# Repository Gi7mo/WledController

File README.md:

# WLED Controller for 5V LED Strips

*e.g. ws2812b, and only tested with them*

The Power supply is a 100-240VAC one and  rated at 5v 4A, don't exceed the power of the supply. Use e.g. the [WLED power calculator](https://wled-calculator.github.io/)

**As i live in germany, the pcb is only tested with 230V AC, if you supply any other voltage, be warned!**

*It can go up in flames, explode or kill you. It's main power!*

- 

**BOM**
|Reference               |Quantity|Value                                                                                                              |LCSC    |ALI                                              |
|------------------------|--------|-------------------------------------------------------------------------------------------------------------------|--------|-------------------------------------------------|
|C1 C2                   |2       |C                                                                                                                  |C107172 |[Link](https://s.click.aliexpress.com/e/_DkweKyn)|
|J1                      |1       |Conn_01x02_Male                                                                                                    |C475092 |[Link](https://s.click.aliexpress.com/e/_DC1TC2L)|
|J2                      |1       |Conn_01x03_Male                                                                                                    |C475093 |[Link](https://s.click.aliexpress.com/e/_DC1TC2L)|
|J3                      |1       |Conn_01x04_Male                                                                                                    |C2691448|[Link](https://s.click.aliexpress.com/e/_DDO0FkL)|
|Q1                      |1       |BSS138                                                                                                             |C52895  |[Link](https://s.click.aliexpress.com/e/_DF4Oc0f)|
|R1 R2 R3 R4 R5 R6 R7    |7       |10K                                                                                                                |C144471 |[Link](https://s.click.aliexpress.com/e/_Ddns0gR)|
|SW1                     |1       |SW_FLASH                                                                                                           |C393938 |[Link](https://s.click.aliexpress.com/e/_DdksuhH)|
|SW2                     |1       |SW_RESET                                                                                                           |C393938 |[Link](https://s.click.aliexpress.com/e/_DdksuhH)|
|U2                      |1       |AMS1117-3.3                                                                                                        |C5199435|[Link](https://s.click.aliexpress.com/e/_DF2uDUr)|
|U3                      |1       |ESP8266-12E/ESP-12E                                                                                                |C82891  |[Link](https://s.click.aliexpress.com/e/_DlO99yR)|
|M3 Threaded Insert      |2       |M3x5x4                                                                                                             |        |[Link](https://s.click.aliexpress.com/e/_DEReEY7)|
|ISO 7380-1 Screws       |2       |M3x6                                                                                                               |        |[Link](https://s.click.aliexpress.com/e/_Dd6fzUn)|
|U1                      |1       |[Meanwell_MPM-20-5](https://www.meanwell-web.com/en-gb/ac-dc-single-output-medical-encapsulated-power-mpm--20--5)  |        |                                                 |
|USB to Serial Converter |OPTIONAL|FT232                                                                                                              |        |[Link](https://s.click.aliexpress.com/e/_DD2GD3H)|

For the Cable Holes i added some [Rubber Cable Rings](https://www.ebay.de/itm/202766961119) with 6mm inner diameter

**Assembly**
- Order the pcb at e.g. [pcbway](https://www.pcbway.com/project/shareproject/WLED_Controller_for_5V_LED_Strips_270c2944.html) or [jlcpcb](https://jlcpcb.com/)
- While you wait, Print the casing
- Assemble the PCB
- use a soldering iron to mount your threaded inserts in the case
- mount the rubber rings, if you brought them
- Check your usb 2 serial converter that it is set to 3.3V (any other voltage will damage the esp8266)
- use the pcb pin headers to wire up the PCB with the usb 2 serial converter
```
┌────────────────────┐
│  VCC  GND  TX  RX  │
│   │    │   │ ┌──┘  │
│   │    │   └─┼──┐  │
│   │    │   ┌─┘  │  │
│   ▼    ▼   ▼    ▼  │
│  VCC  GND  TX  RX  │
└────────────────────┘
```
- while plugging in your usb2searial conveerter, hold down the FLASH button of the pcb
- go to the [WLED web installer](https://install.wled.me/) and flash your board
- setup wifi for your board
- go to the configuration website of your board, select the led setup, the output pin is **GPIO 12**
- now pull your wires through the holes in the case, wire them up to the screw terminals
- put the pcb into the case and put the lid on it

- 
- 

## Notes
- You can contact me via Discord "Gi7mo!#4618"
- This readme file contains Amazon Associate, Aliexpress affiliate, PCBWay affiliate links. I make a comission on qualifying purchases.
- This project does not come with any warranty, if you choose to build/use one, you are doing this at your own risk!
- Be Aware, it can go up in flames, explode, harm you or kill you. Mains power is dangerous!

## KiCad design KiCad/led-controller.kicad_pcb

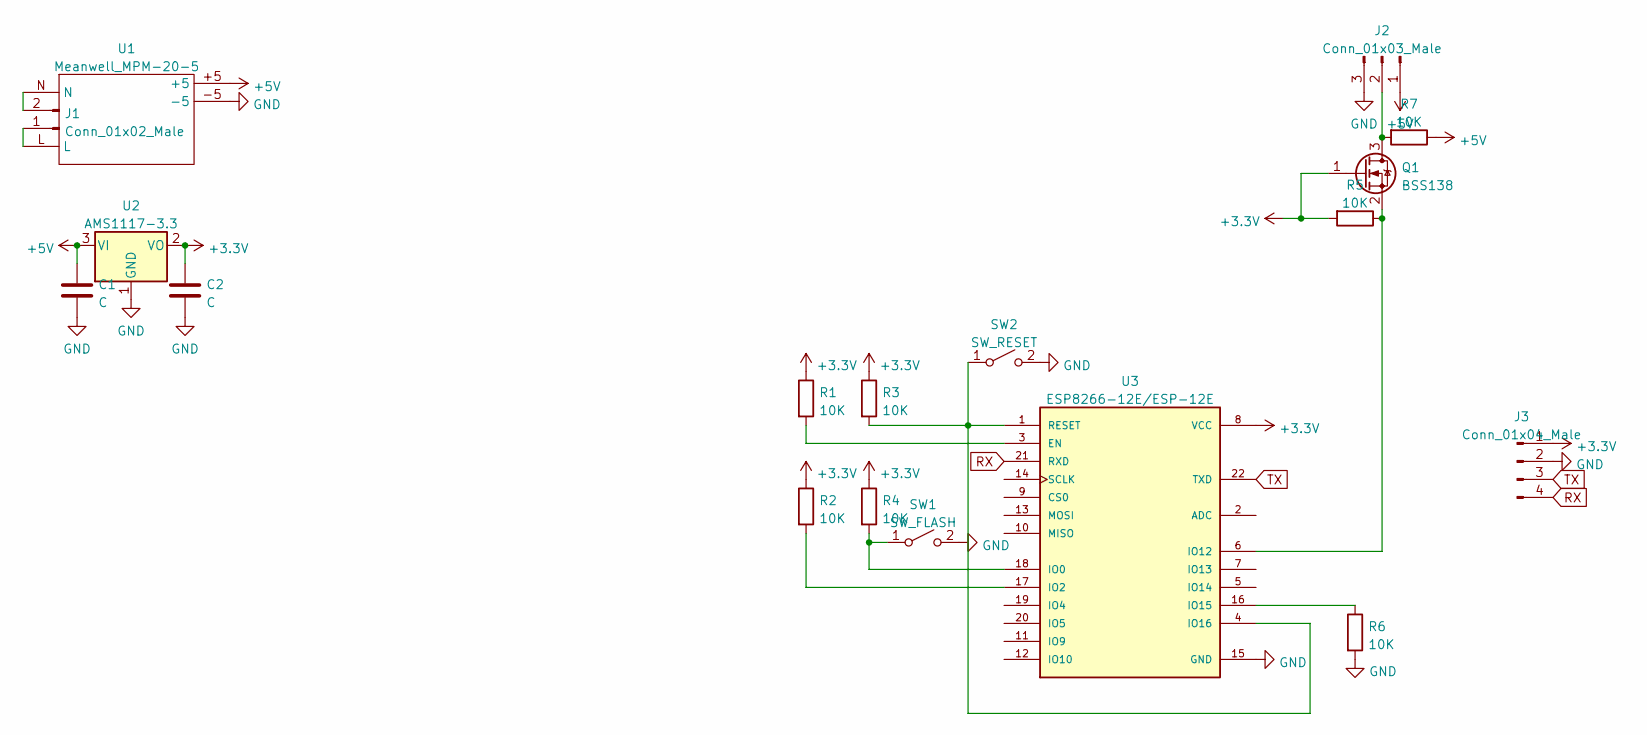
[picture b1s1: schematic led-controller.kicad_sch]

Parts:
C1, C2: C; C_1206_3216Metric; LCSC C107172
J1: Conn_01x02_Male; TerminalBlock_Phoenix_MKDS-3-2-5.08_1x02_P5.08mm_Horizontal; LCSC C475092
J2: Conn_01x03_Male; TerminalBlock_Phoenix_MKDS-3-3-5.08_1x03_P5.08mm_Horizontal; LCSC C475093
J3: Conn_01x04_Male; PinHeader_1x04_P2.54mm_Vertical; LCSC C2691448
Q1: BSS138; SOT-23; LCSC C52895
R1, R2, R3, R4, R5, R6, R7: 10K; R_1206_3216Metric; LCSC C144471
SW1: SW_FLASH; SW_PUSH_6mm; LCSC C393938
SW2: SW_RESET; SW_PUSH_6mm; LCSC C393938
U1: Meanwell_MPM-20-5; Meanwell MPM-20-5
U2: AMS1117-3.3; SOT-223-3_TabPin2; LCSC C5199435
U3: ESP8266-12E/ESP-12E; XCVR_ESP8266-12E/ESP-12E; LCSC C82891

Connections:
+3V3: C2.1, J3.1, Q1.1 (G), R1.1, R2.1, R3.1, R4.1, R5.2, U2.2 (VO), U3.8 (VCC)
+5V: C1.1, J2.1, R7.1, U1.+5, U2.3 (VI)
GND: C1.2, C2.2, J2.3, J3.2, R6.2, SW1.2 (B), SW2.2 (B), U1.-5, U2.1 (GND), U3.15 (GND); also elsewhere on the board
unnamed: J1.1, U1.L
unnamed: J1.2, U1.N
unnamed: J2.2, Q1.3 (D), R7.2
unnamed: Q1.2 (S), R5.1, U3.6 (IO12)
unnamed: R1.2, U3.3 (EN)
unnamed: R2.2, U3.17 (IO2)
unnamed: R3.2, SW2.1 (A), U3.1 (RESET), U3.4 (IO16)
unnamed: R4.2, SW1.1 (A), U3.18 (IO0)
unnamed: R6.1, U3.16 (IO15)
RX: J3.4, U3.21 (RXD)
TX: J3.3, U3.22 (TXD)

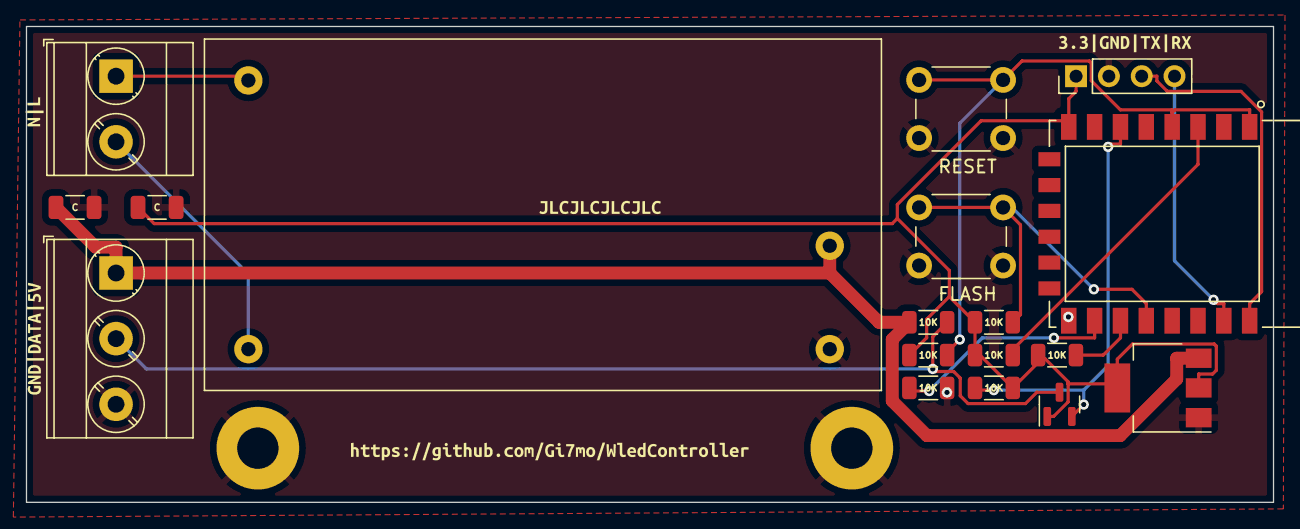
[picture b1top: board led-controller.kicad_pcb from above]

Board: 2 copper layers, 96.5 x 36.8 mm, 24 parts (0 on the bottom side), 14 nets.

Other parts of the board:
hole2: MountingHole_3.2mm_M3_Pad
kibuzzard-638B31F4: G***; kibuzzard-638B31F4
kibuzzard-638B47A7: G***; kibuzzard-638B47A7
kibuzzard-63717C47: G***; kibuzzard-63717C47
kibuzzard-63717C63: G***; kibuzzard-63717C63
kibuzzard-63717D24: G***; kibuzzard-63717D24

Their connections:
GND: hole2.1; also elsewhere on the board

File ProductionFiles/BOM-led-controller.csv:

Comment,Designator,Footprint,LCSC
C,"C1,C2",C_1206_3216Metric,C107172
10K,"R1,R2,R3,R4,R5,R6,R7",R_1206_3216Metric,C144471
Conn_01x04_Male,J3,PinHeader_1x04_P2.54mm_Vertical,C2691448
FLASH,"SW1,SW2",SW_PUSH_6mm,C393938
Conn_01x02_Male,J1,TerminalBlock_Phoenix_MKDS-3-2-5.08_1x02_P5.08mm_Horizontal,C475092
Conn_01x03_Male,J2,TerminalBlock_Phoenix_MKDS-3-3-5.08_1x03_P5.08mm_Horizontal,C475093
AMS1117-3.3,U2,SOT-223-3_TabPin2,C5199435
BSS138,Q1,SOT-23,C52895
ESP8266-12E/ESP-12E,U3,XCVR_ESP8266-12E_ESP-12E,C82891

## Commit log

2022-12-13 roses are red, plus is minus and i fucked up
